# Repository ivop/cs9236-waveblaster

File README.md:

# cs9236-waveblaster

A shrunken version of this design has been sold as the CrystalBlaster C1 IVO edition :)
https://www.serdashop.com/CrystalBlasterC1

Now there's a shrunken SMD version called the CrystalBlaster C2
https://www.serdashop.com/CrystalBlaster-C2

Note that I am not in any way affiliated with the seller. My design is open source and the functionality has not changed. You can build it yourself or buy it :)

https://www.youtube.com/watch?v=O6CxHOC51vI

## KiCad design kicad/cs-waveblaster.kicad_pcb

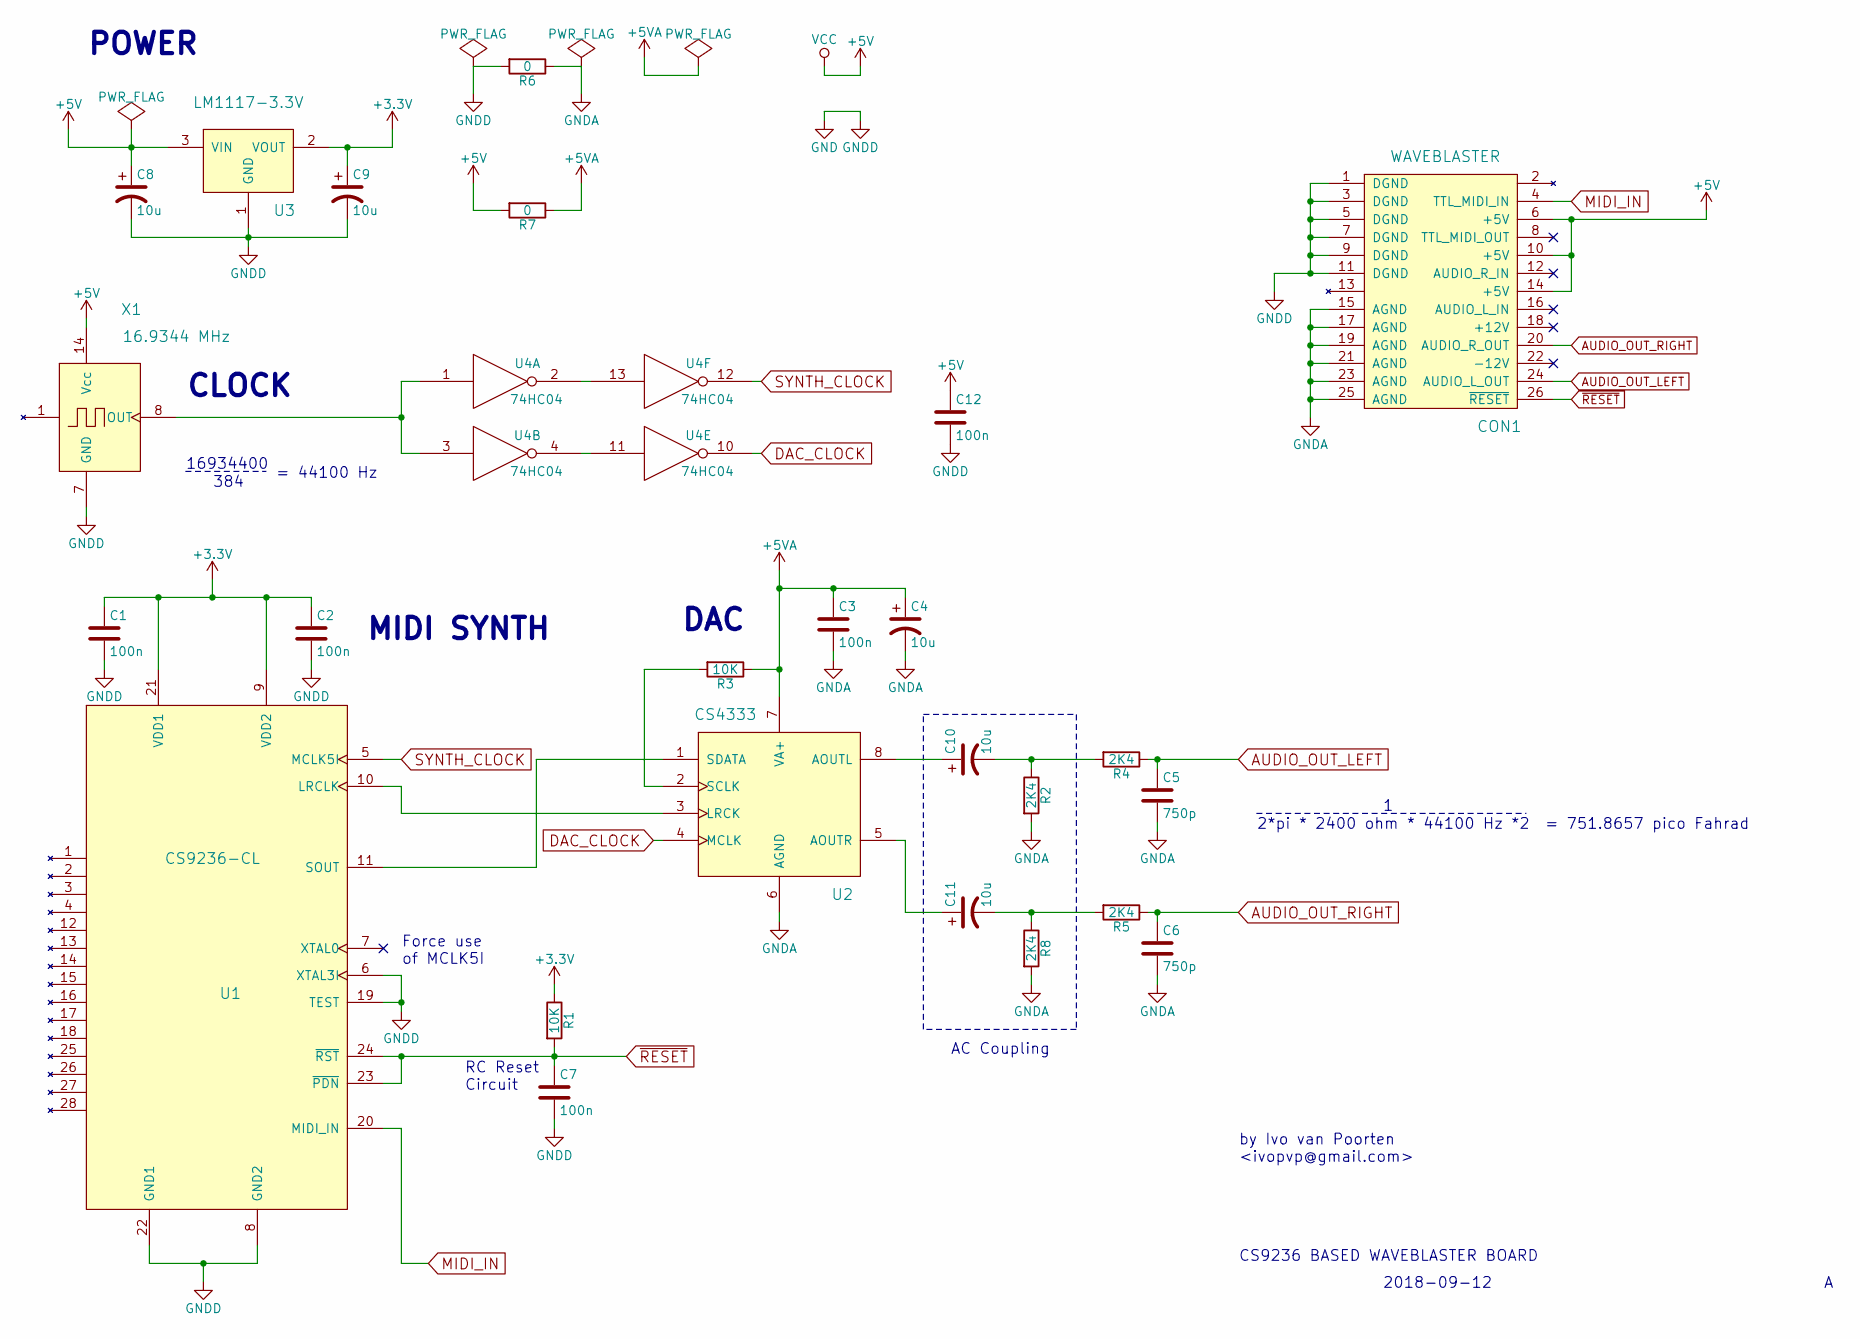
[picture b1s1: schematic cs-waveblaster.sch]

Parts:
C1, C2, C3, C7, C12: 100n; C_Disc_D3_P2.5
C4, C8, C9, C10, C11: 10u; C_Radial_D5_L6_P2.5
C5, C6: 750p; C_Disc_D3_P2.5
CON1: WAVEBLASTER; Pin_Header_Straight_2x13
R1, R3: 10K; Resistor_Horizontal_RM10mm
R2, R4, R5, R8: 2K4; Resistor_Horizontal_RM10mm
R6, R7: 0; Resistor_Horizontal_RM10mm
U1: CS9236-CL; PLCC28
U2: CS4333; SOIC-8-N
U3: LM1117-3.3V; TO-220_Neutral123_Vertical
U4: 74HC04; DIP-14_W7.62mm
X1: 16.9344 MHz; KXO-200_LargePads

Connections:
+3V3: C1.1, C2.1, C9.1, R1.1, U1.9 (VDD2), U1.21 (VDD1), U3.2 (VOUT)
+5V: C8.1, C12.1, CON1.6 (+5V), CON1.10 (+5V), CON1.14 (+5V), R7.2, U3.3 (VIN), U4.14 (VCC), X1.14 (Vcc)
+5VA: C3.1, C4.1, R3.1, R7.1, U2.7 (VA+)
AUDIO_OUT_LEFT: C5.1, CON1.24 (AUDIO_L_OUT), R4.1
AUDIO_OUT_RIGHT: C6.1, CON1.20 (AUDIO_R_OUT), R5.1
DAC_CLOCK: U2.4 (MCLK), U4.10
GND: C1.2, C2.2, C7.2, C8.2, C9.2, C12.2, CON1.1 (DGND), CON1.3 (DGND), CON1.5 (DGND), CON1.7 (DGND), CON1.9 (DGND), CON1.11 (DGND), R6.2, U1.6 (XTAL3I), U1.8 (GND2), U1.19 (TEST), U1.22 (GND1), U3.1 (GND), U4.7 (GND), X1.7 (GND)
GNDA: C3.2, C4.2, C5.2, C6.2, CON1.15 (AGND), CON1.17 (AGND), CON1.19 (AGND), CON1.21 (AGND), CON1.23 (AGND), CON1.25 (AGND), R2.2, R6.1, R8.2, U2.6 (AGND)
MIDI_IN: CON1.4 (TTL_MIDI_IN), U1.20 (MIDI_IN)
unnamed: C10.1, U2.8 (AOUTL)
unnamed: C10.2, R2.1, R4.2
unnamed: C11.1, U2.5 (AOUTR)
unnamed: C11.2, R5.2, R8.1
unnamed: R3.2, U2.2 (SCLK)
unnamed: U1.10 (LRCLK), U2.3 (LRCK)
unnamed: U1.11 (SOUT), U2.1 (SDATA)
unnamed: U4.1, U4.3, X1.8 (OUT)
unnamed: U4.4, U4.11
unnamed: U4.2, U4.13
SYNTH_CLOCK: U1.5 (MCLK5I), U4.12
~RESET: C7.1, CON1.26 (~RESET), R1.2, U1.23 (~PDN), U1.24 (~RST)

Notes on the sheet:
Force use of MCLK5I
RC Reset Circuit
= 751.8657 pico Fahrad
CS9236 BASED WAVEBLASTER BOARD
by Ivo van Poorten <ivopvp@gmail.com>
2018-09-12
2*pi * 2400 ohm * 44100 Hz *2
MIDI SYNTH
DAC
POWER
CLOCK
16934400
384
= 44100 Hz
AC Coupling

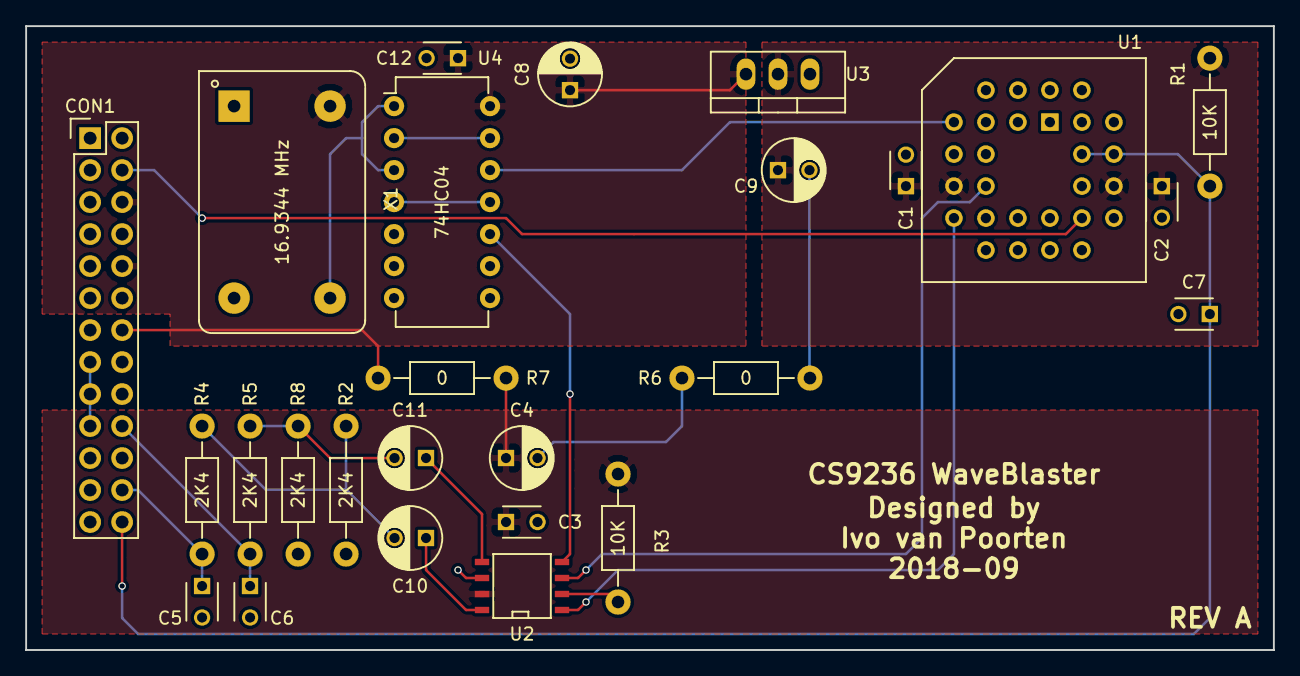
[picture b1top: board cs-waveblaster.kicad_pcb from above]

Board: 2 copper layers, 99.1 x 49.5 mm, 26 parts (0 on the bottom side), 21 nets.

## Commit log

2018-11-02 revision a
2018-11-02 kicad rendering
2018-11-02 add photos
2018-11-02 foo bar
2018-11-02 show photos
2022-04-25 add kicad project
2022-09-10 Link to commercial versions of this open design
